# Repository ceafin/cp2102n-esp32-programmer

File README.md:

# cp2102n-esp32-programmer
CP2102N-A02 based USB-to-UART bridge controller for use in programming ESP32 chips and modules

For an interactive BOM, download and view in browser: [interactive BOM](ibom.html)

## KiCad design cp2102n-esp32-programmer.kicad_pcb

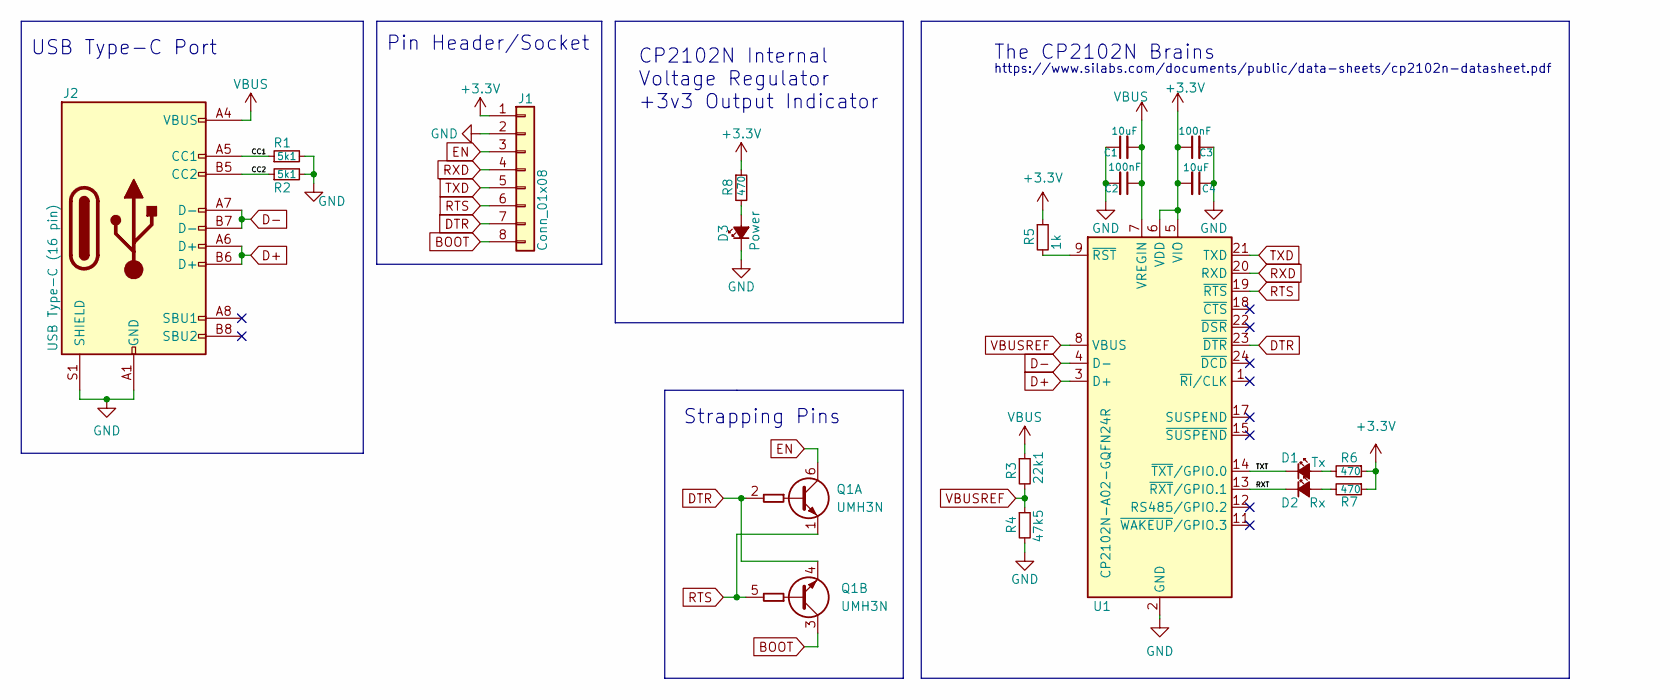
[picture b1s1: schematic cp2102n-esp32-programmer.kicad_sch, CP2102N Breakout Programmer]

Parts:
C1, C4: 10uF; C_0603_1608Metric_Pad1.08x0.95mm_HandSolder; LCSC Prt# C1691
C2, C3: 100nF; C_0603_1608Metric_Pad1.08x0.95mm_HandSolder; LCSC Prt# C30926
D1: Tx; LED_0805_2012Metric_Pad1.15x1.40mm_HandSolder; LCSC Prt# C84258
D2: Rx; LED_0805_2012Metric_Pad1.15x1.40mm_HandSolder; LCSC Prt# C84258
D3: Power; LED_0805_2012Metric_Pad1.15x1.40mm_HandSolder; LCSC Prt# C84256
J1: Conn_01x08; PinHeader_1x08_P2.54mm_Vertical
J2: USB Type-C (16 pin); USB_C_Receptacle_XKB_U262-16XN-4BVC11; LCSC Prt# C319148
Q1: UMH3N; SOT-363_SC-70-6; LCSC Prt# C123008
R1, R2: 5k1; R_0603_1608Metric_Pad0.98x0.95mm_HandSolder; LCSC Prt# C26000
R3: 22k1; R_0603_1608Metric_Pad0.98x0.95mm_HandSolder; LCSC Prt# C310274
R4: 47k5; R_0603_1608Metric_Pad0.98x0.95mm_HandSolder; LCSC Prt# C2933225
R5: 1k; R_0603_1608Metric_Pad0.98x0.95mm_HandSolder; LCSC Prt# C21190
R6, R7, R8: 470; R_0603_1608Metric_Pad0.98x0.95mm_HandSolder; LCSC Prt# C25241
U1: CP2102N-A02-GQFN24R; QFN-24-1EP_4x4mm_P0.5mm_EP2.6x2.6mm; LCSC Prt# C969151

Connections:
+3.3V: C3.1, C4.2, J1.1, R5.1, R6.1, R7.1, R8.1, U1.5 (VIO), U1.6 (VDD)
/CC1: J2.A5 (CC1), R1.1
/CC2: J2.B5 (CC2), R2.1
/RXT: D2.1 (K), U1.13 (~RXT/GPIO.1)
/TXT: D1.1 (K), U1.14 (~TXT/GPIO.0)
BOOT: J1.8, Q1.3 (C2)
D+: J2.A6 (D+), J2.B6 (D+), U1.3 (D+)
D-: J2.A7 (D-), J2.B7 (D-), U1.4 (D-)
DTR: J1.7, Q1.2 (B1), Q1.4 (E2), U1.23 (~DTR)
EN: J1.3, Q1.6 (C1)
GND: C1.1, C2.2, C3.2, C4.1, D3.1 (K), J1.2, J2.A1 (GND), J2.A12 (GND), J2.B1 (GND), J2.B12 (GND), J2.S1 (SHIELD), R1.2, R2.2, R4.2, U1.2 (GND), U1.25 (GND)
unnamed: D1.2 (A), R6.2
unnamed: D2.2 (A), R7.2
unnamed: D3.2 (A), R8.2
unnamed: R5.2, U1.9 (~RST)
RTS: J1.6, Q1.1 (E1), Q1.5 (B2), U1.19 (~RTS)
RXD: J1.4, U1.20 (RXD)
TXD: J1.5, U1.21 (TXD)
VBUS: C1.2, C2.1, J2.A4 (VBUS), J2.A9 (VBUS), J2.B4 (VBUS), J2.B9 (VBUS), R3.1, U1.7 (VREGIN)
VBUSREF: R3.2, R4.1, U1.8 (VBUS)

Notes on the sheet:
USB Type-C Port
https://www.silabs.com/documents/public/data-sheets/cp2102n-datasheet.pdf
Pin Header/Socket
CP2102N Internal Voltage Regulator +3v3 Output Indicator
Strapping Pins
The CP2102N Brains

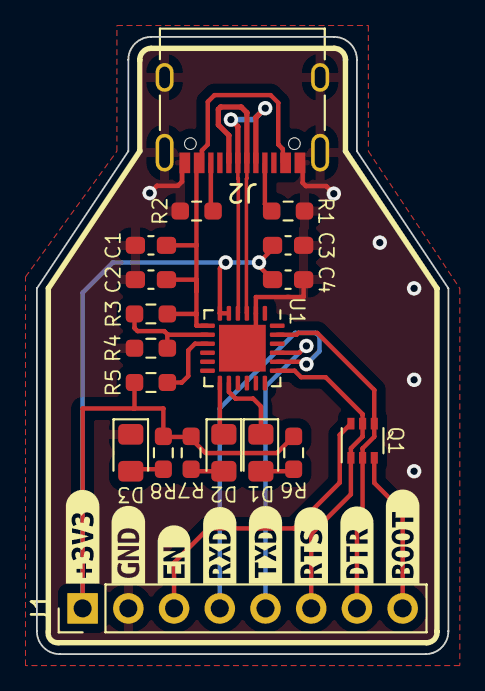
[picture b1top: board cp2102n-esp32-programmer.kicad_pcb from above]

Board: 2 copper layers, 22.9 x 34.3 mm, 27 parts (0 on the bottom side), 20 nets.

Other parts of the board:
kibuzzard-62E5E2EC: G***; kibuzzard-62E5E2EC
kibuzzard-62E5E2FE: G***; kibuzzard-62E5E2FE
kibuzzard-62E5E3A7: G***; kibuzzard-62E5E3A7
kibuzzard-62E5E34B: G***; kibuzzard-62E5E34B
kibuzzard-62E5E36B: G***; kibuzzard-62E5E36B
kibuzzard-62E5E308: G***; kibuzzard-62E5E308
kibuzzard-62E5E316: G***; kibuzzard-62E5E316
kibuzzard-62E5E325: G***; kibuzzard-62E5E325

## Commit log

2022-08-17 Minor Update README.md with license badge and link
2022-08-17 Adding PCB and Schematic
2022-08-17 adding schematic PDF
2022-08-17 adding pcb layout PNG
2022-08-17 adding interactive BOM HTML
2022-08-17 extremely minor change to readme :|

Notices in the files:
README.md:
License: GPL v3
